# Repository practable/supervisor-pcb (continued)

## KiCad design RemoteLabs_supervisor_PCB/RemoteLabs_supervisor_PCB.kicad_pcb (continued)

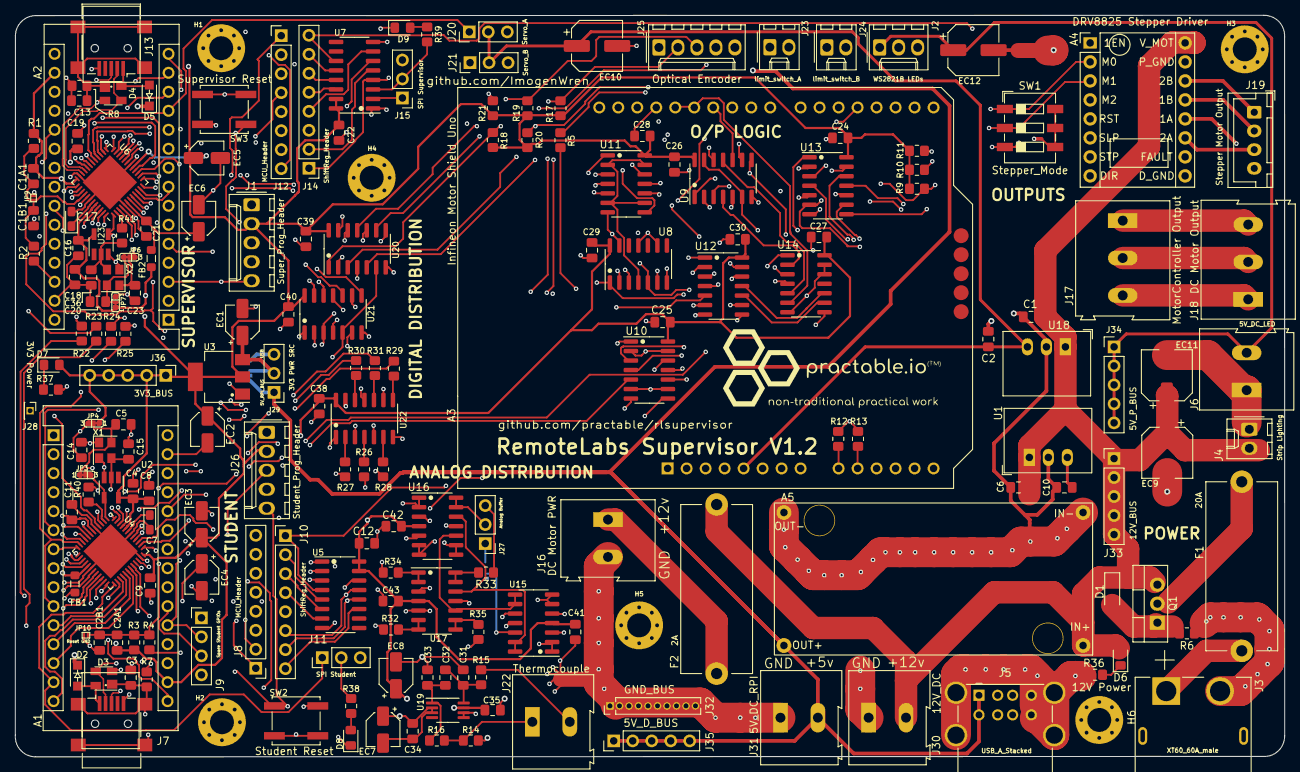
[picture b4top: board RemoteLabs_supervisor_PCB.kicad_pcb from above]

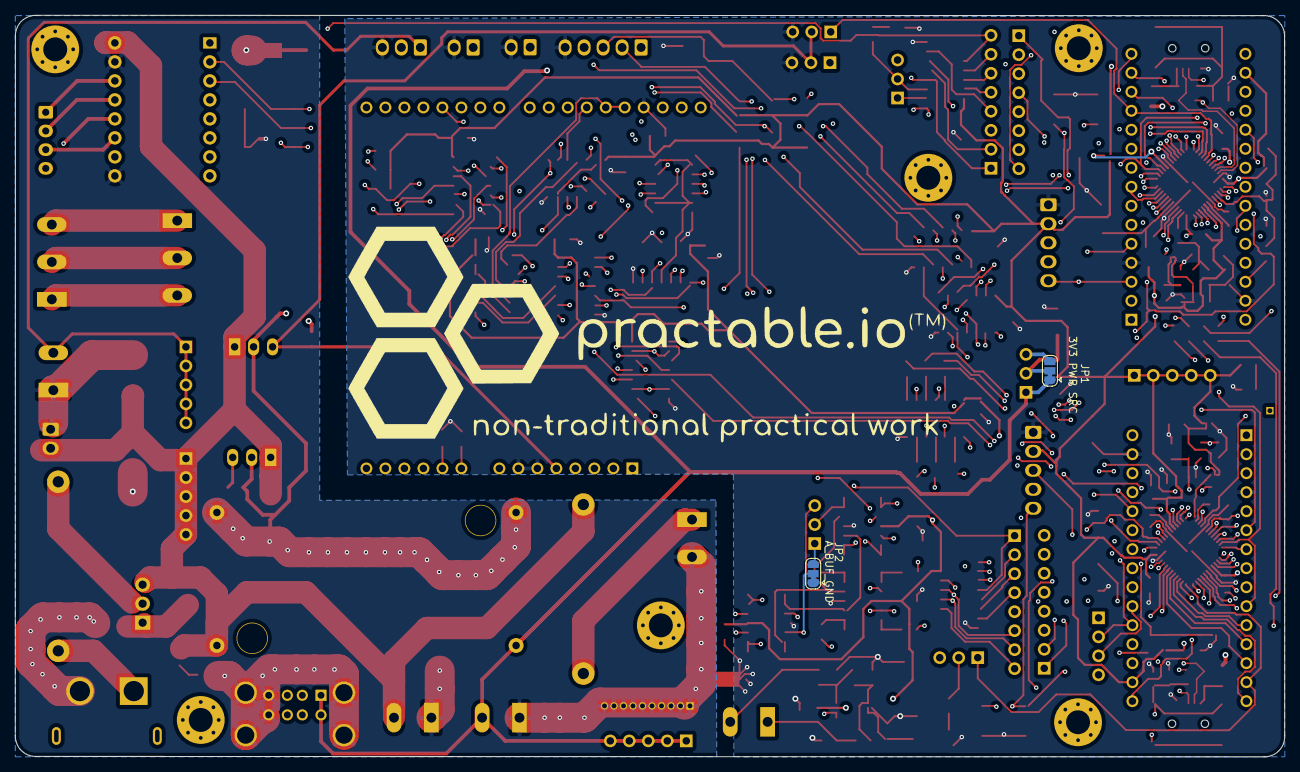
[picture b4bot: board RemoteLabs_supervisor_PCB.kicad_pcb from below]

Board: 4 copper layers, 169.7 x 99.1 mm, 200 parts (2 on the bottom side), 201 nets.

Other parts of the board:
NT4: NetTie_2; NetTie-2_SMD_Pad2.0mm

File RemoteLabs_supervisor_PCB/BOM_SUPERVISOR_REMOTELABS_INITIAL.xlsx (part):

Ref | Qnty | Value | Cmp name | Footprint | Description |  |  | Total Q Part | add 5% | Total Parts Cost | Q Ordered | Vendor Option A | Delivery Expected | Price Per unit | Vendor B | Delivery Expected |  | Price Per unit | FARNELL OC | RS Order Code |  | Notes |  |  |  |  |  |  |  |  |  | Quantity Boards
A1, A2, | 2 | Arduino_Nano_33_IoT | Arduino_Nano_33_IoT | Module:Arduino_Nano | Arduino Nano v2.x |  |  | 160 |  | 2702.4 |  | https://uk.rs-online.com/web/p/arduino/1927585 | IN STOCK | 16.89 |  |  |  |  |  | 192-7585 |  |  |  |  |  |  |  |  |  |  |  | 80
A3, | 1 | Infineon Motor Shield Uno | Infineon Motor Shield Uno | Module:Arduino_UNO_R3 | Arduino UNO Microcontroller Module, release 3 |  |  | 80 |  | 1316.8000000000002 |  | https://uk.rs-online.com/web/p/shields-for-arduino/9062874 | 44701 | 16.46 |  |  |  |  |  | 906-2874 |  |  |  |  |  |  |  |  |  |  |  | 80
A4, | 1 | DRV8825 High Current Stepper Motor Driver Module | DRV8825 High Current Stepper Motor Driver Module | Module:Arduino_UNO_R3 | DRV8825 High Current Stepper Motor Driver Module |  |  | 80 |  | 560 |  | https://www.az-delivery.de/en/products/drv8825-schrittmotor-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 | IN STOCK | 7 |  |  |  |  |  |  |  |  |  |  |  |  |  |  |  |  |  | 80
EC1, EC2, EC3, EC4, EC5, EC6, EC7, EC8, | 8 | 10u | SMD Aluminium Electrolytic Capacitor, Radial Can - SMD, 10 µF, 25 V, 3000 hours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 | Capacitor_SMD:CP_Elec_4x5.4 | Polarized capacitor |  |  | 640 | 670 | 100.5 |  | https://uk.farnell.com/kemet/exv106m025a9baa/cap-10-f-25v-ra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 | IN STOCK | 0.15 |  |  |  |  | 2069174 |  |  |  |  |  |  |  |  |  |  |  |  | 80
EC9, EC10, EC11 | 3 | 100u | SMD Aluminium Electrolytic Capacitor, Radial Can - SMD, 100 µF, 35 V, 2000 hour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 | Capacitor_SMD:CP_Elec_6.3x7.7 | Polarized capacitor |  |  | 240 | 252 | 45.36 |  | https://uk.farnell.com/kemet/edk107m035a9haa/cap-100-f-35v-r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 | IN STOCK | 0.18 |  |  |  |  | 2068675 |  |  |  |  |  |  |  |  |  |  |  |  | 80
C1A1, C2A1, | 2 | 100p | SMD Multilayer Ceramic Capacitor, 100 pF, 50 V, 0805 [2012 Metric], ± 5%, C0G /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 | Capacitor_SMD:C_0805_2012Metric_Pad1.18x1.45mm_HandSolder | Unpolarized capacitor |  |  | 160 | 170 | 8.5 |  | https://uk.farnell.com/avx/08055a101jat2a/cap-100pf-50v-5-c0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 | IN STOCK | 0.05 |  |  |  |  | 2280669 |  |  |  |  |  |  |  |  |  |  |  |  | 80
C1B1, C2B1, | 2 | 100n | SMD Multilayer Ceramic Capacitor, 0.1 µF, 50 V, 0805 [2012 Metric], ± 10%, X7R | Capacitor_SMD:C_0805_2012Metric_Pad1.18x1.45mm_HandSolder | Unpolarized capacitor |  |  | 160 | 168 | 15.12 |  | https://uk.farnell.com/avx/08055c104kat4a/cap-0-1-f-50v-10-x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 | IN STOCK | 0.09 |  | Accounted For Below |  |  | 2332787 |  |  |  |  |  |  |  |  |  |  |  |  | 80
C3, C13, | 2 | 4n7 | SMD Multilayer Ceramic Capacitor, 4700 pF, 50 V, 0805 [2012 Metric], ± 10%, X7R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 | Capacitor_SMD:C_0805_2012Metric_Pad1.18x1.45mm_HandSolder | Unpolarized capacitor |  |  | 160 | 168 | 5.04 |  | https://uk.farnell.com/kemet/c0805c472k5ractu/cap-4700pf-50v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 | IN STOCK | 0.03 |  |  |  |  | 1414696 |  |  |  |  |  |  |  |  |  |  |  |  | 80
C4, C5, C14, C15, | 4 | 9pF | SMD Multilayer Ceramic Capacitor, 9 pF, 50 V, 0805 [2012 Metric], ± 0.5pF, C0G 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 | Capacitor_SMD:C_0805_2012Metric_Pad1.18x1.45mm_HandSolder | Unpolarized capacitor |  |  | 320 | 336 | 13.44 |  | https://uk.farnell.com/multicomp/mc0805n9r0d500ct/cap-9pf-50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 | IN STOCK | 0.04 |  |  |  |  | 1759189 |  |  |  |  |  |  |  |  |  |  |  |  | 80
C7, C17, | 2 | 1u | Surface Mount Tantalum Capacitor, 1 µF, 20 V, 0805 [2012 Metric], ± 10%, 20 ohm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 | Capacitor_SMD:C_0805_2012Metric_Pad1.18x1.45mm_HandSolder | LOW ESR capacitor |  |  | 160 | 168 | 30.24 |  | https://uk.farnell.com/avx/tajr105k020rnj/cap-1-f-20v-10-080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 | 119 in stock | 0.18 | https://uk.farnell.com/avx/tajr105k016rnj/cap-1-f-16v-10-080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 | 55 in stock | 0.28000000000000003 |  | 1432430 | Surface Mount Tantalum Capacitor, 1 µF, 16 V, 0805 [2012 Metric], ± 10%, 20 ohm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 |  | 1658936RL |  |  |  |  |  |  |  |  |  | 80
C8, C9, C11, C12, C18, C19, C21, C22, C24, C25, C26, C27, C28, C29, C30, C31, C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 | 28 | 100n | SMD Multilayer Ceramic Capacitor, 0.1 µF, 50 V, 0805 [2012 Metric], ± 10%, X7R | Capacitor_SMD:C_0805_2012Metric_Pad1.18x1.45mm_HandSolder | Unpolarized capacitor |  |  | 2240 | 2352 | 47.04 |  | https://uk.farnell.com/avx/08055c104kat4a/cap-0-1-f-50v-10-x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 | IN STOCK | 0.02 |  |  |  |  | 2280669 |  |  |  |  |  |  |  |  |  |  |  |  | 80
D1, | 1 | BZV55B9V1 | Zener Single Diode, 9.1 V, 400 mW, SOD-80C, 2 %, 2 Pins, 200 °C | Diode_SMD:D_MiniMELF | 9.1V, 500mW, 2%, Zener diode, MiniMELF |  |  | 80 | 84 | 11.760000000000002 |  | https://uk.farnell.com/nexperia/bzv55-b9v1-115/diode-zener-9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 | 44683 | 0.14000000000000001 |  |  |  |  | 2319152 |  |  |  |  |  |  |  |  |  |  |  |  | 80
D2, D5, | 2 | PMEG6020ER | PMEG6020ER | Diode_SMD:Nexperia_CFP3_SOD-123W | 60V, 2A low Vf MEGA Schottky barrier rectifier, SOD-123W |  |  | 160 | 168 | 42 |  | https://uk.farnell.com/nexperia/pmeg6020er-115/diode-schottk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 | 44833 | 0.25 |  |  |  |  |  |  |  |  |  |  |  |  |  |  |  |  |  | 80
D3, D4, | 2 | PRTR5V0U2X | ESD Protection Device, TVS, 7.5 V, SOT-143B, 4 Pins, 5.5 V, PRTR5 | Package_TO_SOT_SMD:SOT-143 | Ultra low capacitance double rail-to-rail ESD protection diode, SOT-143 |  |  | 160 | 168 | 52.08 |  | https://uk.farnell.com/nexperia/prtr5v0u2x-215/diode-tvs-dua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 | IN STOCK | 0.31 |  |  |  |  | 1524157RL |  |  |  |  |  |  |  |  |  |  |  |  | 80
D6, | 3 | 12v Power Led | LED, Blue, SMD, 0805 [2012 Metric], 20 mA, 3.4 V, 475 nm |  | RED or BLUE |  |  | 240 | 252 | 25.200000000000003 |  | https://uk.farnell.com/multicomp-pro/mp008292/led-blue-210mc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 | IN STOCK | 0.1 |  | added extra for pin 13 LED |  |  | 3796324 |  |  |  |  |  |  |  |  |  |  |  |  | 80
D7, | 1 | 3V3 Power Led | LED, Low Power, Orange, SMD, 0805 [2012 Metric], 20 mA, 2.1 V, 601 nm |  | Orange |  |  | 80 | 100 | 14.000000000000002 |  | https://uk.farnell.com/kingbright/kp-2012seck/led-0805-250mc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 | IN STOCK | 0.14000000000000001 |  |  |  |  | 2290332 |  |  |  |  |  |  |  |  |  |  |  |  | 80
F1, | 2 | 20A | Fuseholder, Open Design, 250V, 10A, 5 x 20mm, Through Hole, Black | Fuse:Fuseholder_Cylinder-5x20mm_Stelvio-Kontek_PTF78_Horizontal_Open | Fuse |  |  | 160 | 168 | 223.44 |  | https://uk.farnell.com/littelfuse/65600001009/fuseholder-5x2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 | IN STOCK | 1.33 |  |  |  |  | 1597013 |  |  | 10A Holder |  |  |  |  |  |  |  |  |  | 80
F2, | 1 | 2A | Fuseholder, Open Design, 250V, 10A, 5 x 20mm, Through Hole, Black | Fuse:Fuseholder_Cylinder-5x20mm_Stelvio-Kontek_PTF78_Horizontal_Open | Fuse |  |  | 80 | 84 | 111.72 |  | https://uk.farnell.com/littelfuse/65600001009/fuseholder-5x2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 | IN STOCK | 1.33 |  |  | Accounted for above |  | 1597013 |  |  | 10A Holder |  |  |  |  |  |  |  |  |  | 80
 |  |  |  |  |  |  |  | 0 | 0 | 0 |  |  |  |  |  |  |  |  |  |  |  |  |  |  |  |  |  |  |  |  |  | 80
FB1, FB2, | 2 | BLM18PG471 | FerriteBead_Small | Inductor_SMD:L_0805_2012Metric_Pad1.05x1.20mm_HandSolder | Ferrite bead, small symbol |  |  | 160 | 1 pack of 200 | 6.8 |  | https://uk.rs-online.com/web/p/ferrite-beads/1048535 | IN STOCK | 3.4000000000000002E-2 |  |  |  |  |  | 104-8535 |  |  |  |  |  |  |  |  |  |  |  | 80
Generic Pin Headers |  |  |  |  |  |  |  | 0 | 0 | 0 |  |  |  |  |  |  |  |  |  |  |  |  |  |  |  |  |  |  |  |  |  | 80
J1, J25, J26, | 3 | prog headers & OE | Pin Header, Square Pin, Signal, Wire-to-Board, 2.54 mm, 1 Rows, 5 Contacts, Thr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 | Connector_PinHeader_2.54mm:PinHeader_1x05_P2.54mm_Vertical | Needs to be populated |  |  | 240 | 252 | 128.52000000000001 |  | https://uk.farnell.com/molex/22-27-2051/connector-header-5po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 | IN STOCK | 0.51 |  |  |  |  | 9731679 |  |  |  |  |  |  |  |  |  |  |  |  | 80
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
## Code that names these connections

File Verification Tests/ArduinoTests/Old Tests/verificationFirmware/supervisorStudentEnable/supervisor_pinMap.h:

/*  #Remote Labs Supervisor MCU PinMap
*   
*     Imogen Heard
*     25/05/2022
*
*/

#ifndef supervisor_pinMap_h
#define supervisor_pinMap_h



// Arduino Compatable Pins

//Inputs
 
#define ENCODER_B           2
#define ENCODER_A           3
#define ENCODER_INDEX       4

#define STDNT_DC_M_DIR_2    14
#define STDNT_DC_M_DIR_1    15

#define STEPP_FLT           19

#define LIMIT_1             18


#define STDNT_SRVO_RX_1     A2      // STDNT_SRVO_RX_2 Only available on SAMD21 Raw

#define THERMO              A3

#define DC_MOTOR_IS2        A6
#define DC_MOTOR_IS1        A7


// Outputs

#define DC_MOTOR_PWM        10
#define DC_MOTOR_DIR1       12
#define DC_MOTOR_DIR2       7

#define STEPP_STEP          6

#define SERVO_1             9

#define PIXEL_DATA          5

// Shift Register
#define MOSI                11
#define SCK                 13
#define LATCH               8



// Shift Register Pins [Output Only] (needs shiftRegister.h to validate)

#define DC_MOTOR_EN          Q0
#define STUDENT_M_EN         Q1
#define STUDENT_STEP_EN      Q2
#define STUDENT_PIXEL_EN     Q3
#define STEPP_DIR            Q4
#define STEPP_EN             Q5
#define STEPP_RST            Q6
#define SHIFT_REG_7          Q7












#endif

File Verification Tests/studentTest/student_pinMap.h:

/*  #Remote Labs Supervisor MCU PinMap
*   
*	Imogen Heard
*	25/05/2022
*
*/

#ifndef supervisor_pinMap_h
#define supervisor_pinMap_h




// Arduino Compatable Pins


#define ENCODER_B				    2
#define ENCODER_A				    3
#define ENCODER_INDEX		   	4
#define PIXEL_DATA				  5
#define STEPP_STEP 				  6
#define DC_MOTOR_DIR2			  7
#define LATCH				      	8
#define SERVO_1					    9
#define DC_MOTOR_PWM		   	10
#define	MOSI					      11
#define DC_MOTOR_DIR1			  12
#define SCK						      13
#define SPARE_1					    15     // <- not the same as Supervisor
#define LIMIT_1					    18
#define STEPP_FLT			    	19

#define SPARE_2	    				A2
#define THERMO				    	A3
#define DC_MOTOR_IS2	  		A6
#define DC_MOTOR_IS1	  		A7


// Shift Register Pins (Needs shiftRegister.h to validate)

#define DC_MOTOR_EN			  	Q0
#define SHIFT_1	    				Q1
#define SHIFT_2			    		Q2
#define SHIFT_3			    		Q3
#define STEPP_DIR			    	Q4
#define STEPP_EN	    			Q5
#define STEPP_RST	    			Q6
#define SHIFT_REG_7		   		Q7












#endif

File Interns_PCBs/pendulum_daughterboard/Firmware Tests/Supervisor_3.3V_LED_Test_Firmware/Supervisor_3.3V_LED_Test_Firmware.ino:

#include "supervisor_pinMap.h"

#include "shiftRegister.h"

//Assigning names for the function of the pendulum board

#define SUP_LED_1 DC_MOTOR_DIR1

#define SUP_LED_2 DC_MOTOR_DIR2

#define SUP_LED_3 SERVO_1

#define STU_ENABLE STUDENT_M_EN

#define DRIVE DC_MOTOR_EN

#define LOAD STEPP_STEP

shiftRegister shiftReg(MOSI, SCK, LATCH);



void setup() {
  // put your setup code here, to run once:

  pinMode (SUP_LED_1, OUTPUT);
  pinMode (SUP_LED_2, OUTPUT);
  pinMode (SUP_LED_3, OUTPUT);
  pinMode (STU_ENABLE, OUTPUT);
  pinMode (DRIVE, OUTPUT);
  pinMode (LOAD, OUTPUT);
  shiftReg.begin();


//flashLED();
}



void loop() {
//Initially setting all the pins low


 shiftReg.shiftWrite(DRIVE, LOW);  
 digitalWrite (LOAD, LOW); 
 shiftReg.shiftWrite(STU_ENABLE, LOW);
 digitalWrite (SUP_LED_1, HIGH);
 digitalWrite (SUP_LED_2, HIGH);
 digitalWrite (SUP_LED_3, HIGH);

  // Trying to turn the pins on without enable

  //delay(3000);
//  digitalWrite (STU_LED_1, HIGH);
 // delay(1000);
  //digitalWrite (STU_LED_1,  LOW);
  //digitalWrite (STU_LED_2, HIGH);
 // delay(1000);
  //digitalWrite (STU_LED_2, LOW);
  //digitalWrite (STU_LED_3, HIGH);
  //delay(1000);
  //digitalWrite (STU_LED_3, LOW);
  //digitalWrite (SUP_LED_1, HIGH);
  //delay(1000);
  //digitalWrite (SUP_LED_1, LOW);
  //digitalWrite (SUP_LED_2, HIGH);
 // delay(1000);
  //digitalWrite (SUP_LED_2, LOW);
 // digitalWrite (SUP_LED_3, HIGH);

  // Trying to turn the pins on with enable
 // delay(1000);
 // digitalWrite (STU_ENABLE, HIGH);
 // delay(1000);
 // digitalWrite (SUP_LED_3, LOW);
//  digitalWrite (STU_LED_1, HIGH);
 // delay(1000);
//  digitalWrite (STU_LED_1,  LOW);
//  digitalWrite (STU_LED_2, HIGH);
//  delay(1000);
 // digitalWrite (STU_LED_2, LOW);
 // digitalWrite (STU_LED_3, HIGH);
 // delay(1000);
 // digitalWrite (STU_LED_3, LOW);
 // digitalWrite (SUP_LED_1, HIGH);
 // delay(1000);
 // digitalWrite (SUP_LED_1, LOW);
 // digitalWrite (SUP_LED_2, HIGH);
 // delay(1000);
 // digitalWrite (SUP_LED_2, LOW);
  //digitalWrite (SUP_LED_3, HIGH);



}


void flashLED() {
  int count = 6;
  while (count) {
    digitalWrite (SUP_LED_1, HIGH);
    delay(500);
    digitalWrite (SUP_LED_1,  LOW);
    delay(200);
    count--;
  }
}

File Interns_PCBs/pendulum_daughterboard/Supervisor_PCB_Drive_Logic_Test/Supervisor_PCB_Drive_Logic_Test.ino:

#include "supervisor_pinMap.h"

#include "shiftFunctions.h"  

void setup() {
  // put your setup code here, to run once:
//  pinMode (STU_LED_1, OUTPUT);
//  pinMode (STU_LED_2, OUTPUT);
//  pinMode (STU_LED_3, OUTPUT);
  pinMode (DC_MOTOR_DIR1, OUTPUT);
  pinMode (DC_MOTOR_DIR2, OUTPUT);
  pinMode (SERVO_1, OUTPUT);
  pinMode (STUDENT_M_EN, OUTPUT);
  pinMode (DC_MOTOR_EN, OUTPUT);
  pinMode (STEPP_STEP, OUTPUT);
}

void loop() {
  // put your main code here, to run repeatedly:

 digitalWrite (DC_MOTOR_EN, LOW); //drive
 digitalWrite (STEPP_STEP, LOW); //load

 if (digitalRead(DC_MOTOR_EN) == LOW  && digitalRead(STEPP_STEP) == LOW)
  {
    digitalWrite(DC_MOTOR_DIR1, HIGH);
  }

  if ( digitalRead(DC_MOTOR_EN) == HIGH  && digitalRead(STEPP_STEP) == LOW)
  {
    digitalWrite(DC_MOTOR_DIR2, HIGH);
  }

  if (digitalRead(DC_MOTOR_EN) == LOW  && digitalRead(STEPP_STEP) == HIGH)
  {
    digitalWrite(SERVO_1, HIGH);
  }

  
  if (digitalRead(DC_MOTOR_EN) == HIGH  && digitalRead(STEPP_STEP) == HIGH)
  {
    digitalWrite(SERVO_1, HIGH);
    digitalWrite(DC_MOTOR_DIR1, HIGH);
    digitalWrite(DC_MOTOR_DIR2, HIGH);
  }

}

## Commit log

2022-03-23 added kicad files
2022-03-23 updated requirements
2022-03-25 updating repo
2022-03-31 Adding to requirements
2022-04-07 started working on schematic
2022-04-08 Schematric work
2022-04-15 changed many things
2022-04-18 adding test sketch
2022-04-19 Motor Shield Test Sketch Written
2022-04-20 \zfsdf
2022-04-21 Schematic Work
2022-04-22 lunchtime backup
2022-04-22 Circuit Design 85-90% complete
2022-04-25 nearing circut deisng complete
2022-04-26 V1.0 Circuit Design Complete
2022-04-26 ERC checks run
2022-04-27 Schematic reviewed
2022-04-29 mbncmvbc,
2022-05-02 Finished BOM and purchasing
2022-05-03 Footprint Association Underway
2022-05-04 Stocktaking
2022-05-05 Finished Ordering and stock control
2022-05-05 Problems with power consumption
    Added additional power bus, annoying and expensive but best action
2022-05-10 Footprint associations complete
2022-05-11 Started PCB layout
2022-05-12 PCB layout
2022-05-14 added kicad themes
2022-05-14 version one finished excluding net ties
2022-05-14 created backup kicad folder
2022-05-14 routing board layout 2.0
2022-05-15 2 am save
2022-05-15 2:01 am save going to bed
2022-05-15 Version 2 PCB Layout
2022-05-15 Board V2 Finished
2022-05-16 Added graphics and 3D model screenshots
2022-05-16 Added fabrication outputs and organised folders
2022-05-24 xcfg
2022-05-25 Added documentation for testing
    Added pin declarations headers
    outlined requirements for test firmware for PCB verification
2022-05-25 added first stage of verification firmware
2022-05-26 added lots to documentation and test firmware
2022-05-26 dfgd
2022-05-27 added functions to test firmware
2022-05-31 added pixel text functions
2022-06-01 changed folders and added optical encoder functions to supervisor test
2022-06-02 updated tests
2022-06-02 adding to test software
2022-06-03 dfbd
2022-06-03 Optical Encoder working
    Still to test
    Stepper motor
    Limit Switches
    Some other things
2022-06-06 Test software mostly tested - awaiting hardware
2022-06-07 wert
2022-06-08 jsadf
2022-06-09 created folder for pendulum driver daughterboard
2022-06-09 Added schematic photos
2022-06-09 added BOMs
2022-06-10 Edited PCB design for V1.1
    - Changed pin sizes for stepper motor
    - Change pin sizes for DC/DC Buck module.
    - In process of changing text to be readable by human beings
2022-06-13 Updated PCB for V1.1 see CHANGELOG
    Test software refinement
2022-06-13 sdfsdf
2022-06-14 cleaned up servo and LED code
2022-06-14 added test for stepper
2022-06-14 Many Changes
2022-06-14 fixed student softare
2022-06-14 Updated some shite
2022-06-14 changes to motor code
2022-06-15 currentsense changes
2022-06-15 Ahhhhhhhhhhhhhhh
2022-06-17 Testing Documentation and Pin Read Test
2022-06-17 Testing Documentation
2022-06-21 Version 1.2 PCB
2022-06-21 Added Pendulum Driver PCB Files
2022-06-22 Today's Progress on the PCB
    22/06/22
2022-06-23 changes
    11.50
2022-06-23 Changes to the PCB
    23/06/2022
2022-06-24 Penduino Daughterboard Update
    The complete design before checks.
2022-06-24 Penduino Board Update
2022-06-24 Add PCB for RasPi Hat
2022-06-24 added files
2022-06-24 Fixed Silkscreen
2022-06-24 changed file structure
2022-06-24 Changed Diode
2022-06-24 Added fabrication template for in house PCB production
2022-06-24 Changes with the Components
2022-06-24 Friday Updates
    24/06/22
2022-06-25 New Design for Outsourcıng
    Added a new design that can be outsourced from a manufacturer. It includes smaller track widths, clearences, via diameter and hole size. Making the design more compact.
2022-06-28 sdfgsrfg
2022-06-30 Fabrication Files
2022-07-01 01/07 UPDATES
2022-07-04 Just updating
2022-07-04 Changed Logic
2022-07-05 Pull down and Current Limiting Resistors
2022-07-06 Pendulum PCB Version 2
2022-07-06 One Connection Left
2022-07-07 attiny 85 pendulum logic
2022-07-07 Pendulum Driver PCB Vol3
    With pull down resistors
2022-07-07 sdfs
2022-07-07 Added population BOM
2022-07-08 sdgfdr
2022-07-11 Flipped Diode on schematic
2022-07-11 edited CSV
2022-07-15 changes on driver PCB
2022-07-15 Added README for Supervisor Motherboard Use Cases
2022-07-18 Added readme for PCB use cases
2022-07-18 werf
2022-07-19 Added Unit Tests and Population Spreadsheet
2022-07-28 changes on 27/07
2022-07-28 Added Documentation for UART and Unit Tests
2022-08-03 new design pendulum PCB
2022-08-03 moved folders
2022-08-05 Everything
2022-08-05 Another Drive PCB
2022-08-08 3.3V PCB Design
    PCB with 2 voltage regulators, regulating both the 5V input from the digital pins and the external 5V from the terminal block.
2022-08-09 Penduino Daughterboard with Level Shifter
2022-08-09 Pin update
2022-08-10 new PCB design started
2022-08-10 Level Shifting Daughterboard
2022-08-11 Truss Test
2023-07-03 renamed files started dev for version 3.0
2023-07-03 removed long filenames
2023-07-03 just getting repo back to safe
2024-10-11 Unknown Changes
2024-10-11 backup files
2025-07-25 Update fp-info-cache
